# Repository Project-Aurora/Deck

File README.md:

# Deck
Breakout Boards for 64-Pin ARM MCUs, Keyswitches and IS31FL3732

# Components
+	MCU: The Microcontroller including one IS31FL3732 and a hot-pluggable Power-Connector (either Barrel Jack or MicroUSB)
+	Chain-Connector: Adds the Possibility to Connect two Devices over UART, an additional Master Pin enables automatic Crossover.
+	CherryMX-RGB: Breakout-Board for a single MX-Type Switch with either SMD or THT Backlighting. A Diode on the Back allows for "Ghostless" Operation. A 1-Wire EEPROM could enable Autodetection of different Switches/LEDs as well as Analog Input Devices.
+	LED-Driver: Breakout-Board for one IS31FL3732. These Boards are Chainable, the Device-Address can be freely assigned using external Connections. The Number of Boards can be enumerated using A/D-Conversion on chained Resistors.

Further Description in the Directories.

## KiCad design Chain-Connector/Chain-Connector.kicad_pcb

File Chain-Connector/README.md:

Chain-Connector: Adds the Possibility to Connect two Devices over UART, an additional Master Pin enables automatic Crossover.

U1 Passes the [1-4]B Input to [1-4]Y when A/B is pulled high, otherwise it [1-4]A is passed through.
The Master Pin serves as A/B and is pulled high when the MCU has succsessfully established Connectivity to a USB-Host.
The "A" state of the Switch means IO1 serves as RX0 and IO2 as TX0.
The "B" state of the Switch means IO1 serves as TX0 and IO2 as RX0.
Because of this the UART-Connection can only be established when one of the two Devices has a USB-Connection, meaning the "RX" of Device1 is connected to Device2's "TX" and vice-versa.
D1 and D2 are needed because connecting the non "TX0" state of 1A and 4B to Ground would pull RX0 low. The EEPROM-Logic doesn't allow for undefined States, thus requireing some kind of connection.
A "Master-LED" (D3) lights up when the Master-Pin is pulled high.

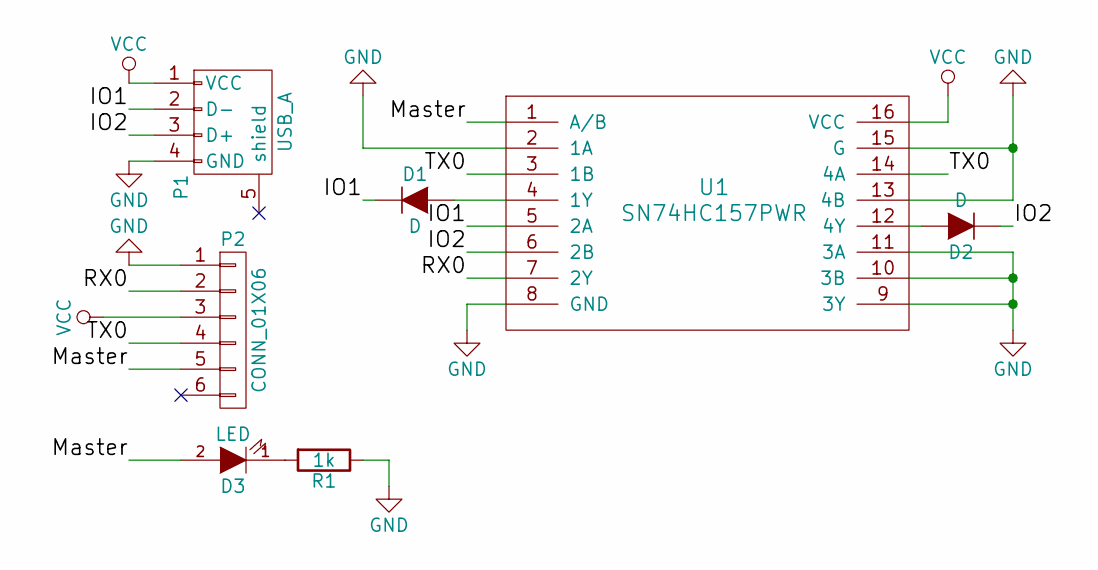
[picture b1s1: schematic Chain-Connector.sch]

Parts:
D1, D2: D; SOD-123
D3: LED; LED_0805
P1: USB_A
P2: CONN_01X06; Pin_Header_Straight_2x03
R1: 1k; R_0603
U1: SN74HC157PWR; TSSOP-16_4.4x5mm_Pitch0.65mm

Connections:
/IO1: D1.1 (K), P1.2 (D-), U1.5 (2A); also elsewhere on the board
/IO2: D2.1 (K), P1.3 (D+), U1.6 (2B); also elsewhere on the board
/Master: D3.2 (A), P2.5, U1.1 (A/B)
/RX0: P2.2, U1.7 (2Y)
/TX0: P2.4, U1.3 (1B), U1.14 (4A)
GND: P1.4 (GND), P2.1, R1.1, U1.2 (1A), U1.8 (GND), U1.9 (3Y), U1.10 (3B), U1.11 (3A), U1.13 (4B), U1.15 (G); also elsewhere on the board
unnamed: D1.2 (A), U1.4 (1Y)
unnamed: D2.2 (A), U1.12 (4Y)
unnamed: D3.1 (K), R1.2
VCC: P1.1 (VCC), P2.3, U1.16 (VCC); also elsewhere on the board

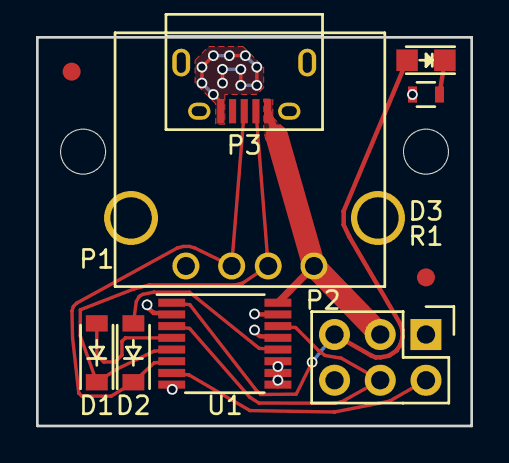
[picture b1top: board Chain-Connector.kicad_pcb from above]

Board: 2 copper layers, 24.1 x 21.6 mm, 8 parts (0 on the bottom side), 10 nets.

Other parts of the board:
P3: USB_OTG; USB_Micro-B

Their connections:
/IO1: P3.2; also elsewhere on the board
/IO2: P3.3; also elsewhere on the board
GND: P3.5; also elsewhere on the board
VCC: P3.1; also elsewhere on the board

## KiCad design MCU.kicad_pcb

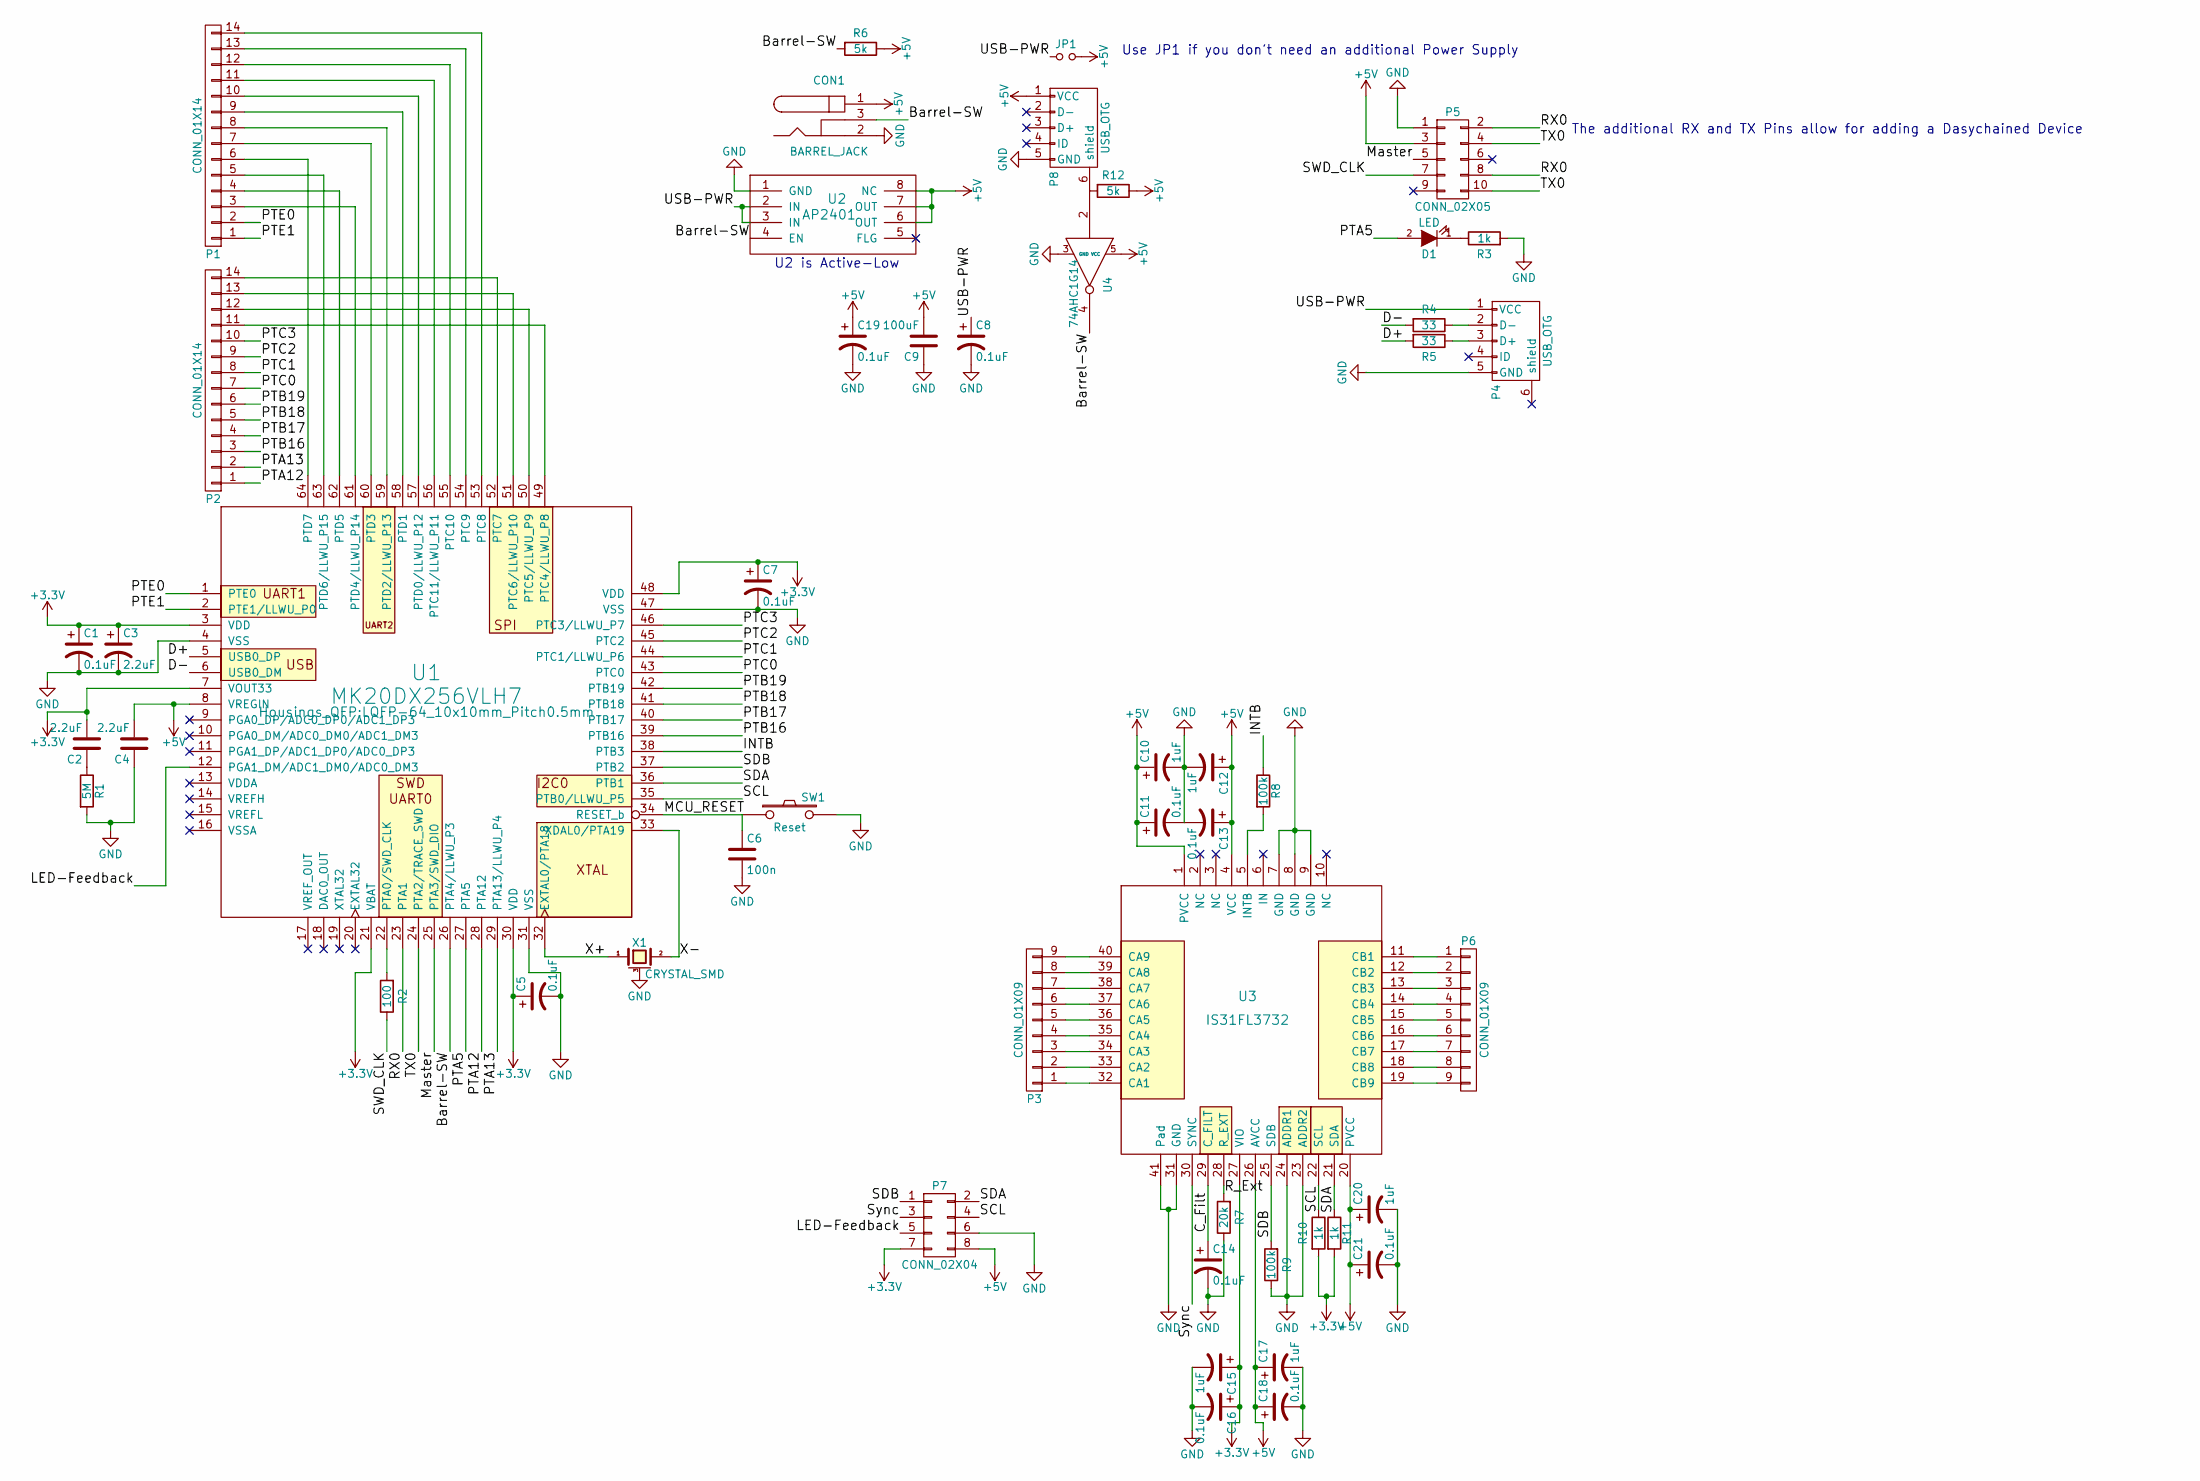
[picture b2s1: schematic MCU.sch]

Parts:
C1, C5, C7, C8, C11, C13, C14, C16, C18, C19, C21: 0.1uF; C_0603
C2, C3, C4: 2.2uF; C_0603
C6: 100n; C_0603
C9: 100uF; C_0805
C10, C12, C15, C17, C20: 1uF; C_0603
CON1: BARREL_JACK
D1: LED; LED_0805
JP1: Jumper_NO_Small; C_0805
P1, P2: CONN_01X14; Pin_Header_Straight_2x07
P3, P6: CONN_01X09; Pin_Header_Straight_1x09
P4, P8: USB_OTG; USB_Micro-B
P5: CONN_02X05; Pin_Header_Straight_2x05
P7: CONN_02X04; Pin_Header_Straight_2x04
R1: 5M; R_0805
R2: 100; R_0603
R3, R10, R11: 1k; R_0603
R4, R5: 33; R_0603
R6, R12: 5k; R_0603
R7: 20k; R_0603
R8, R9: 100k; R_0603
SW1: Reset; SW_Tactile_SPST_Angled
U1: MK20DX256VLH7; LQFP-64_10x10mm_Pitch0.5mm
U2: AP2401; SO-8
U3: IS31FL3732; UQFN-40-1EP_5x5mm_Pitch0.4mm
U4: 74AHC1G14; SOT-353
X1: CRYSTAL_SMD; crystal_FA238-TSX3225

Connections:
+3V3: C1.1, C2.2, C3.1, C5.1, C7.1, C15.1, C16.1, P7.7, R10.2, R11.2, U1.3 (VDD), U1.7 (VOUT33), U1.13 (VDDA), U1.14 (VREFH), U1.17 (VREF_OUT), U1.21 (VBAT), U1.30 (VDD), U1.48 (VDD), U3.27 (VIO); also elsewhere on the board
+5V: C4.2, C9.2, C10.1, C11.1, C12.1, C13.1, C17.1, C18.1, C19.1, C20.1, C21.1, CON1.1, JP1.2, P5.3, P7.8, P8.1 (VCC), R6.1, R12.1, U1.8 (VREGIN), U2.6 (OUT), U2.7 (OUT), U2.8 (NC), U3.1 (PVCC), U3.4 (VCC), U3.20 (PVCC), U3.26 (AVCC), U4.5 (VCC)
/Barrel-SW: CON1.3, R6.2, U1.26 (PTA4/LLWU_P3), U2.4 (EN), U4.4
/C_Filt: C14.1, U3.29 (C_FILT)
/D+: R5.2, U1.5 (USB0_DP)
/D-: R4.2, U1.6 (USB0_DM)
/INTB: R8.1, U1.38 (PTB3)
/LED-FB: P7.5, U1.12 (PGA1_DM/ADC1_DM0/ADC0_DM3)
/MCU_RESET: C6.1, SW1.1, U1.34 (RESET_b)
/Master: P5.5, U1.25 (PTA3/SWD_DIO)
/PTA5: D1.2 (A), U1.27 (PTA5)
/PTA12: P2.1, U1.28 (PTA12)
/PTA13: P2.2, U1.29 (PTA13/LLWU_P4)
/PTB16: P2.3, U1.39 (PTB16)
/PTB17: P2.4, U1.40 (PTB17)
/PTB18: P2.5, U1.41 (PTB18)
/PTB19: P2.6, U1.42 (PTB19)
/PTC0: P2.7, U1.43 (PTC0)
/PTC1: P2.8, U1.44 (PTC1/LLWU_P6)
/PTC2: P2.9, U1.45 (PTC2)
/PTC3: P2.10, U1.46 (PTC3/LLWU_P7)
/PTE0: P1.2, U1.1 (PTE0)
/PTE1: P1.1, U1.2 (PTE1/LLWU_P0)
/RX0: P5.2, P5.8, U1.23 (PTA1)
/R_Ext: R7.2, U3.28 (R_EXT)
/SCL: P7.4, R10.1, U1.35 (PTB0/LLWU_P5), U3.22 (SCL)
/SDA: P7.2, R11.1, U1.36 (PTB1), U3.21 (SDA)
/SDB: P7.1, R9.2, U1.37 (PTB2), U3.25 (SDB)
/SWD_CLK: P5.7, R2.1
/Sync: P7.3, U3.30 (SYNC)
/TX0: P5.4, P5.10, U1.24 (PTA2/TRACE_SWD)
/USB-PWR: C8.1, JP1.1, P4.1 (VCC), U2.2 (IN), U2.3 (IN)
/X+: U1.32 (EXTAL0/PTA18), X1.1
/X-: U1.33 (XDAL0/PTA19), X1.2
GND: C1.2, C3.2, C4.1, C5.2, C6.2, C7.2, C8.2, C9.1, C10.2, C11.2, C12.2, C13.2, C14.2, C15.2, C16.2, C17.2, C18.2, C19.2, C20.2, C21.2, CON1.2, P4.5 (GND), P5.1, P7.6, P8.5 (GND), R1.2, R3.2, R7.1, R9.1, SW1.2, U1.4 (VSS), U1.15 (VREFL), U1.16 (VSSA), U1.31 (VSS), U1.47 (VSS), U2.1 (GND), U3.7 (GND), U3.8 (GND), U3.9 (GND), U3.23 (ADDR2), U3.24 (ADDR1), U3.31 (GND), U3.41 (Pad), U4.3 (GND), X1.3 (case); also elsewhere on the board
unnamed: C2.1, R1.1
unnamed: D1.1 (K), R3.1
unnamed: P1.3, U1.61 (PTD4/LLWU_P14)
unnamed: P1.4, U1.62 (PTD5)
unnamed: P1.5, U1.63 (PTD6/LLWU_P15)
unnamed: P1.6, U1.64 (PTD7)
unnamed: P1.7, U1.60 (PTD3)
unnamed: P1.8, U1.59 (PTD2/LLWU_P13)
unnamed: P1.9, U1.58 (PTD1)
unnamed: P1.10, U1.57 (PTD0/LLWU_P12)
unnamed: P1.11, U1.56 (PTC11/LLWU_P11)
unnamed: P1.12, U1.55 (PTC10)
unnamed: P1.13, U1.54 (PTC9)
unnamed: P1.14, U1.53 (PTC8)
unnamed: P2.11, U1.49 (PTC4/LLWU_P8)
unnamed: P2.12, U1.50 (PTC5/LLWU_P9)
unnamed: P2.13, U1.51 (PTC6/LLWU_P10)
unnamed: P2.14, U1.52 (PTC7)
unnamed: P3.1, U3.32 (CA1)
unnamed: P3.2, U3.33 (CA2)
unnamed: P3.3, U3.34 (CA3)
unnamed: P3.4, U3.35 (CA4)
unnamed: P3.5, U3.36 (CA5)
unnamed: P3.6, U3.37 (CA6)
unnamed: P3.7, U3.38 (CA7)
unnamed: P3.8, U3.39 (CA8)
unnamed: P3.9, U3.40 (CA9)
unnamed: P4.2 (D-), R4.1
unnamed: P4.3 (D+), R5.1
unnamed: P6.1, U3.11 (CB1)
unnamed: P6.2, U3.12 (CB2)
unnamed: P6.3, U3.13 (CB3)
unnamed: P6.4, U3.14 (CB4)
unnamed: P6.5, U3.15 (CB5)
unnamed: P6.6, U3.16 (CB6)
unnamed: P6.7, U3.17 (CB7)
unnamed: P6.8, U3.18 (CB8)
unnamed: P6.9, U3.19 (CB9)
unnamed: P8.6 (shield), R12.2, U4.2
unnamed: R2.2, U1.22 (PTA0/SWD_CLK)
unnamed: R8.2, U3.5 (INTB)

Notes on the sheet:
Use JP1 if you don't need an additional Power Supply
U2 is Active-Low
The additional RX and TX Pins allow for adding a Dasychained Device

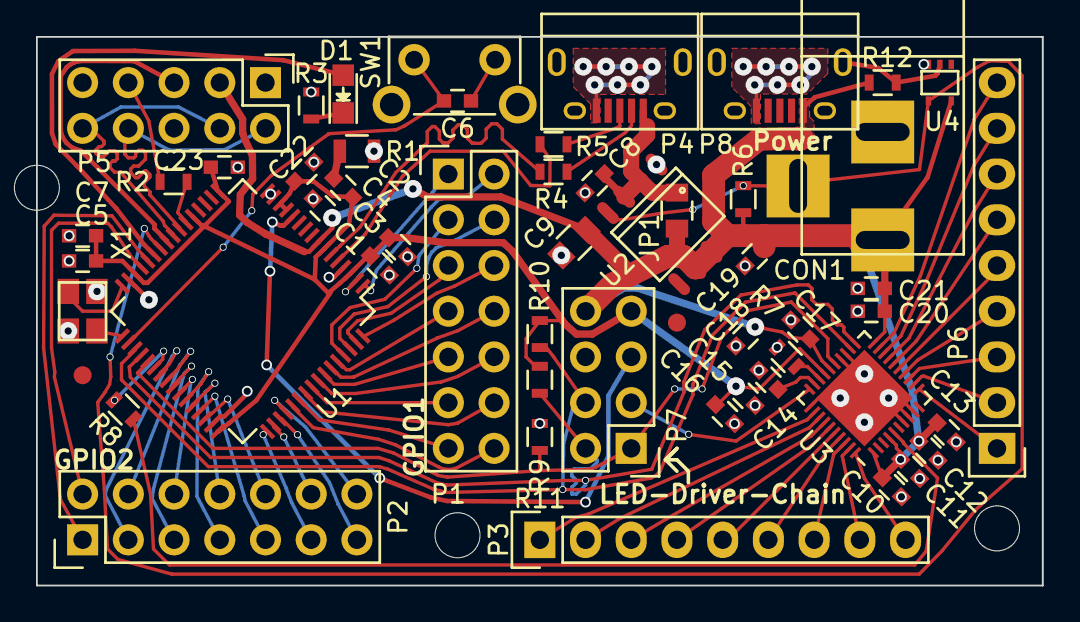
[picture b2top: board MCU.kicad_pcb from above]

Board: 2 copper layers, 55.9 x 30.5 mm, 52 parts (0 on the bottom side), 76 nets.

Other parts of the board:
C22, C23: 0.1uF; C_0603

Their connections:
+3V3: C22.1, C23.1; also elsewhere on the board
GND: C22.2, C23.2; also elsewhere on the board

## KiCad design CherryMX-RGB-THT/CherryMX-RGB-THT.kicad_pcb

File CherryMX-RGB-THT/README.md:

CherryMX-RGB-SMD: Breakout-Board for a single MX-Type Switch with THT Backlighting. A Diode on the Back allows for "Ghostless" Operation. A 1-Wire EEPROM could enable Autodetection of different Switches/LEDs as well as Analog Input Devices.

The EEPROM is powered by the Row(3.3V) and Column(GND), because of this the Boards location in the Matrix can be determined despite the EEPROMs Address being fixed.

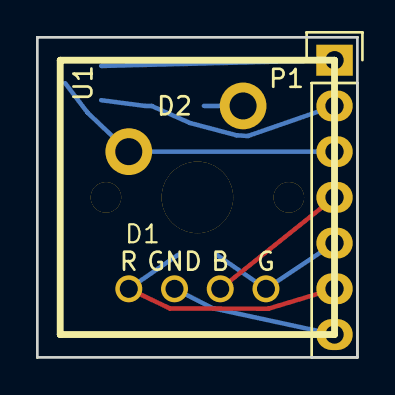
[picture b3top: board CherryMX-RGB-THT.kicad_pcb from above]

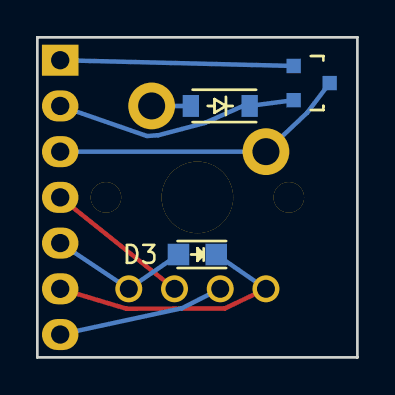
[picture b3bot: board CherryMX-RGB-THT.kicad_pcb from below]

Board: 2 copper layers, 17.8 x 17.8 mm, 6 parts (3 on the bottom side), 8 nets.

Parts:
D1: Led_RGB_CA; RGB
D2: D; SOD-123
D3: LED; LED_0805
P1: CONN_01X07; Pin_Header_Straight_1x07
SW1: SW_PUSH; MX1A
U1: 11AA010T; SOT-23

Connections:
/Col: P1.3, SW1.1, U1.3
/LED-1: D1.1, P1.7
/LED-2: D1.2, D3.1, P1.6
/LED-3: D1.3, D3.2, P1.5
/LED-4: D1.4, P1.4
/Row: D2.1, P1.2, U1.2
/SCIO: P1.1, U1.1
unnamed: D2.2, SW1.2

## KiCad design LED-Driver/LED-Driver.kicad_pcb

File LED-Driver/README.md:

LED-Driver: Breakout-Board for one IS31FL3732. These Boards are Chainable, the Device-Address can be freely assigned using external Connections. The Number of Boards can be enumerated using A/D-Conversion on chained Resistors.

P3 offers the Pins necessary to set the Address-Pins on P4.
A table in the bottom right Corner shows an Overview of the Slave-ID(Columns) as well as the required Connections too ADDR1/s(Rows).

JP1 should be bridged on the last Device in Chain, shorting Feedback-IN to 3.3V.
R1 decreases the resulting current on each Device, allowing an AD-Converter Pin on the MCU to "guesstimate" the number of Resistors in Series and thus the Number of Slaves.

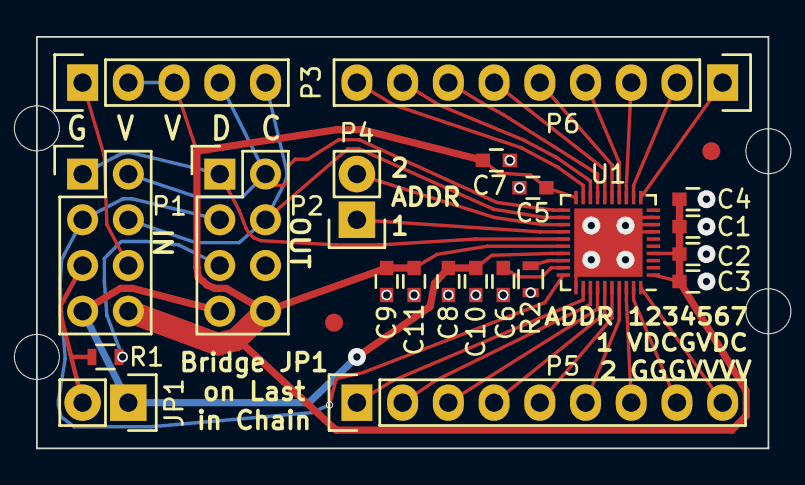
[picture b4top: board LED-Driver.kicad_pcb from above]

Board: 2 copper layers, 40.6 x 22.9 mm, 21 parts (0 on the bottom side), 31 nets.

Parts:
C1, C2, C5, C8, C9: 1uF; C_0603
C3, C4, C6, C7, C10, C11: 0.1uF; C_0603
JP1: Jumper_NO_Small; Pin_Header_Straight_1x02
P1, P2: CONN_02X04; Pin_Header_Straight_2x04
P3: CONN_01X05; Pin_Header_Straight_1x05
P4: CONN_01X02; Pin_Header_Straight_1x02
P5, P6: CONN_01X09; Pin_Header_Straight_1x09
R1: 1234; R_0603
R2: 20k; R_0603
U1: IS31FL3732; UQFN-40-1EP_5x5mm_Pitch0.4mm

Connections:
+3V3: C8.1, C10.1, JP1.1, P1.7, P2.7, U1.27
+5V: C1.1, C2.1, C3.1, C4.1, C5.1, C7.1, C9.1, C11.1, P1.8, P2.8, P3.2, P3.3, U1.1, U1.4, U1.20, U1.26
/ADDR1: P4.1, U1.24
/ADDR2: P4.2, U1.23
/C_Filt: C6.1, U1.29
/Feedback-IN: JP1.2, P1.5, R1.1
/Feedback-OUT: P2.5, R1.2
/R_Ext: R2.2, U1.28
/SCL: P1.4, P2.4, P3.5, U1.22
/SDA: P1.2, P2.2, P3.4, U1.21
/SDB: P1.1, P2.1, U1.25
/Sync: P1.3, P2.3, U1.30
GND: C1.2, C2.2, C3.2, C4.2, C5.2, C6.2, C7.2, C8.2, C9.2, C10.2, C11.2, P1.6, P2.6, P3.1, R2.1, U1.7, U1.8, U1.9, U1.31, U1.41
unnamed: P5.1, U1.32
unnamed: P5.2, U1.33
unnamed: P5.3, U1.34
unnamed: P5.4, U1.35
unnamed: P5.5, U1.36
unnamed: P5.6, U1.37
unnamed: P5.7, U1.38
unnamed: P5.8, U1.39
unnamed: P5.9, U1.40
unnamed: P6.1, U1.11
unnamed: P6.2, U1.12
unnamed: P6.3, U1.13
unnamed: P6.4, U1.14
unnamed: P6.5, U1.15
unnamed: P6.6, U1.16
unnamed: P6.7, U1.17
unnamed: P6.8, U1.18
unnamed: P6.9, U1.19

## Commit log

2016-04-29 Add Files
2016-04-29 Added Readmes to the Subdirectorys
    Fixed placement of some Silkscreen-Stuff on the LED-Driver as well.
2016-04-29 Added Readmes to the Subdirectorys
2016-05-01 Added Analog-Digital Conversion Capability
2016-05-02 Made PCB more Manufacturer-friendly
2016-05-04 Switched to 2.5mm Mounting Holes
2016-05-04 More appropriate Placement of Mounting-Holes
2016-05-05 Added the Option to use an SMD-LED on Backside
    When using a single-color THT LED on the Front
2016-05-08 Minor cleanups
2016-05-08 Adjusted a Trace on the Chain-Connector as well
2016-05-10 Added the Option to use a Micro-USB Connector
    And also revamped the Routing to be less of a Mess
